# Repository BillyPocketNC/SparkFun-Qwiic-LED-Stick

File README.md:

SparkFun Qwiic LED Stick

This Design has been modified to make a 3x3 LED Matrix.
Sparkfun is the original source of the unmodified design.

========================================

[*Qwiic LED Stick (SPX-14783)*](https://www.sparkfun.com/products/14783)

The Qwiic LED Stick features ten addressable APA102 LEDs, making it easy to add full color LED control using I<sup>2</sup>C. Write to individual LEDs to display a count in binary, or write to the whole strip for cool lighting effects. We’ve written an Arduino library that takes care of the I<sup>2</sup>C and communication to the LEDs so all you have to do is decide what color each LED should be.

This board is one of our many [Qwiic](https://www.sparkfun.com/qwiic) compatible boards! Simply plug and go. No soldering, no figuring out which is SDA or SCL, and no voltage regulation or translation required!

SparkFun labored with love to create this code. Feel like supporting open source hardware? 
Buy a [board](https://www.sparkfun.com/products/14783) from SparkFun!

Repository Contents
-------------------

* **/Firmware** - Firmware
* **/Hardware** - Eagle design files (.brd, .sch)

Library
--------------
* **[Arduino Library](https://github.com/sparkfun/SparkFun_Qwiic_LED_Stick_Arduino_Library)** - Library for Qwiic LED Stick

License Information
-------------------

This product is _**open source**_! 

If you have any questions or concerns on licensing, please contact techsupport@sparkfun.com.

Please use, reuse, and modify these files as you see fit. Please maintain attribution to SparkFun Electronics and release any derivative under the same license.

Distributed as-is; no warranty is given.

- Your friends at SparkFun.

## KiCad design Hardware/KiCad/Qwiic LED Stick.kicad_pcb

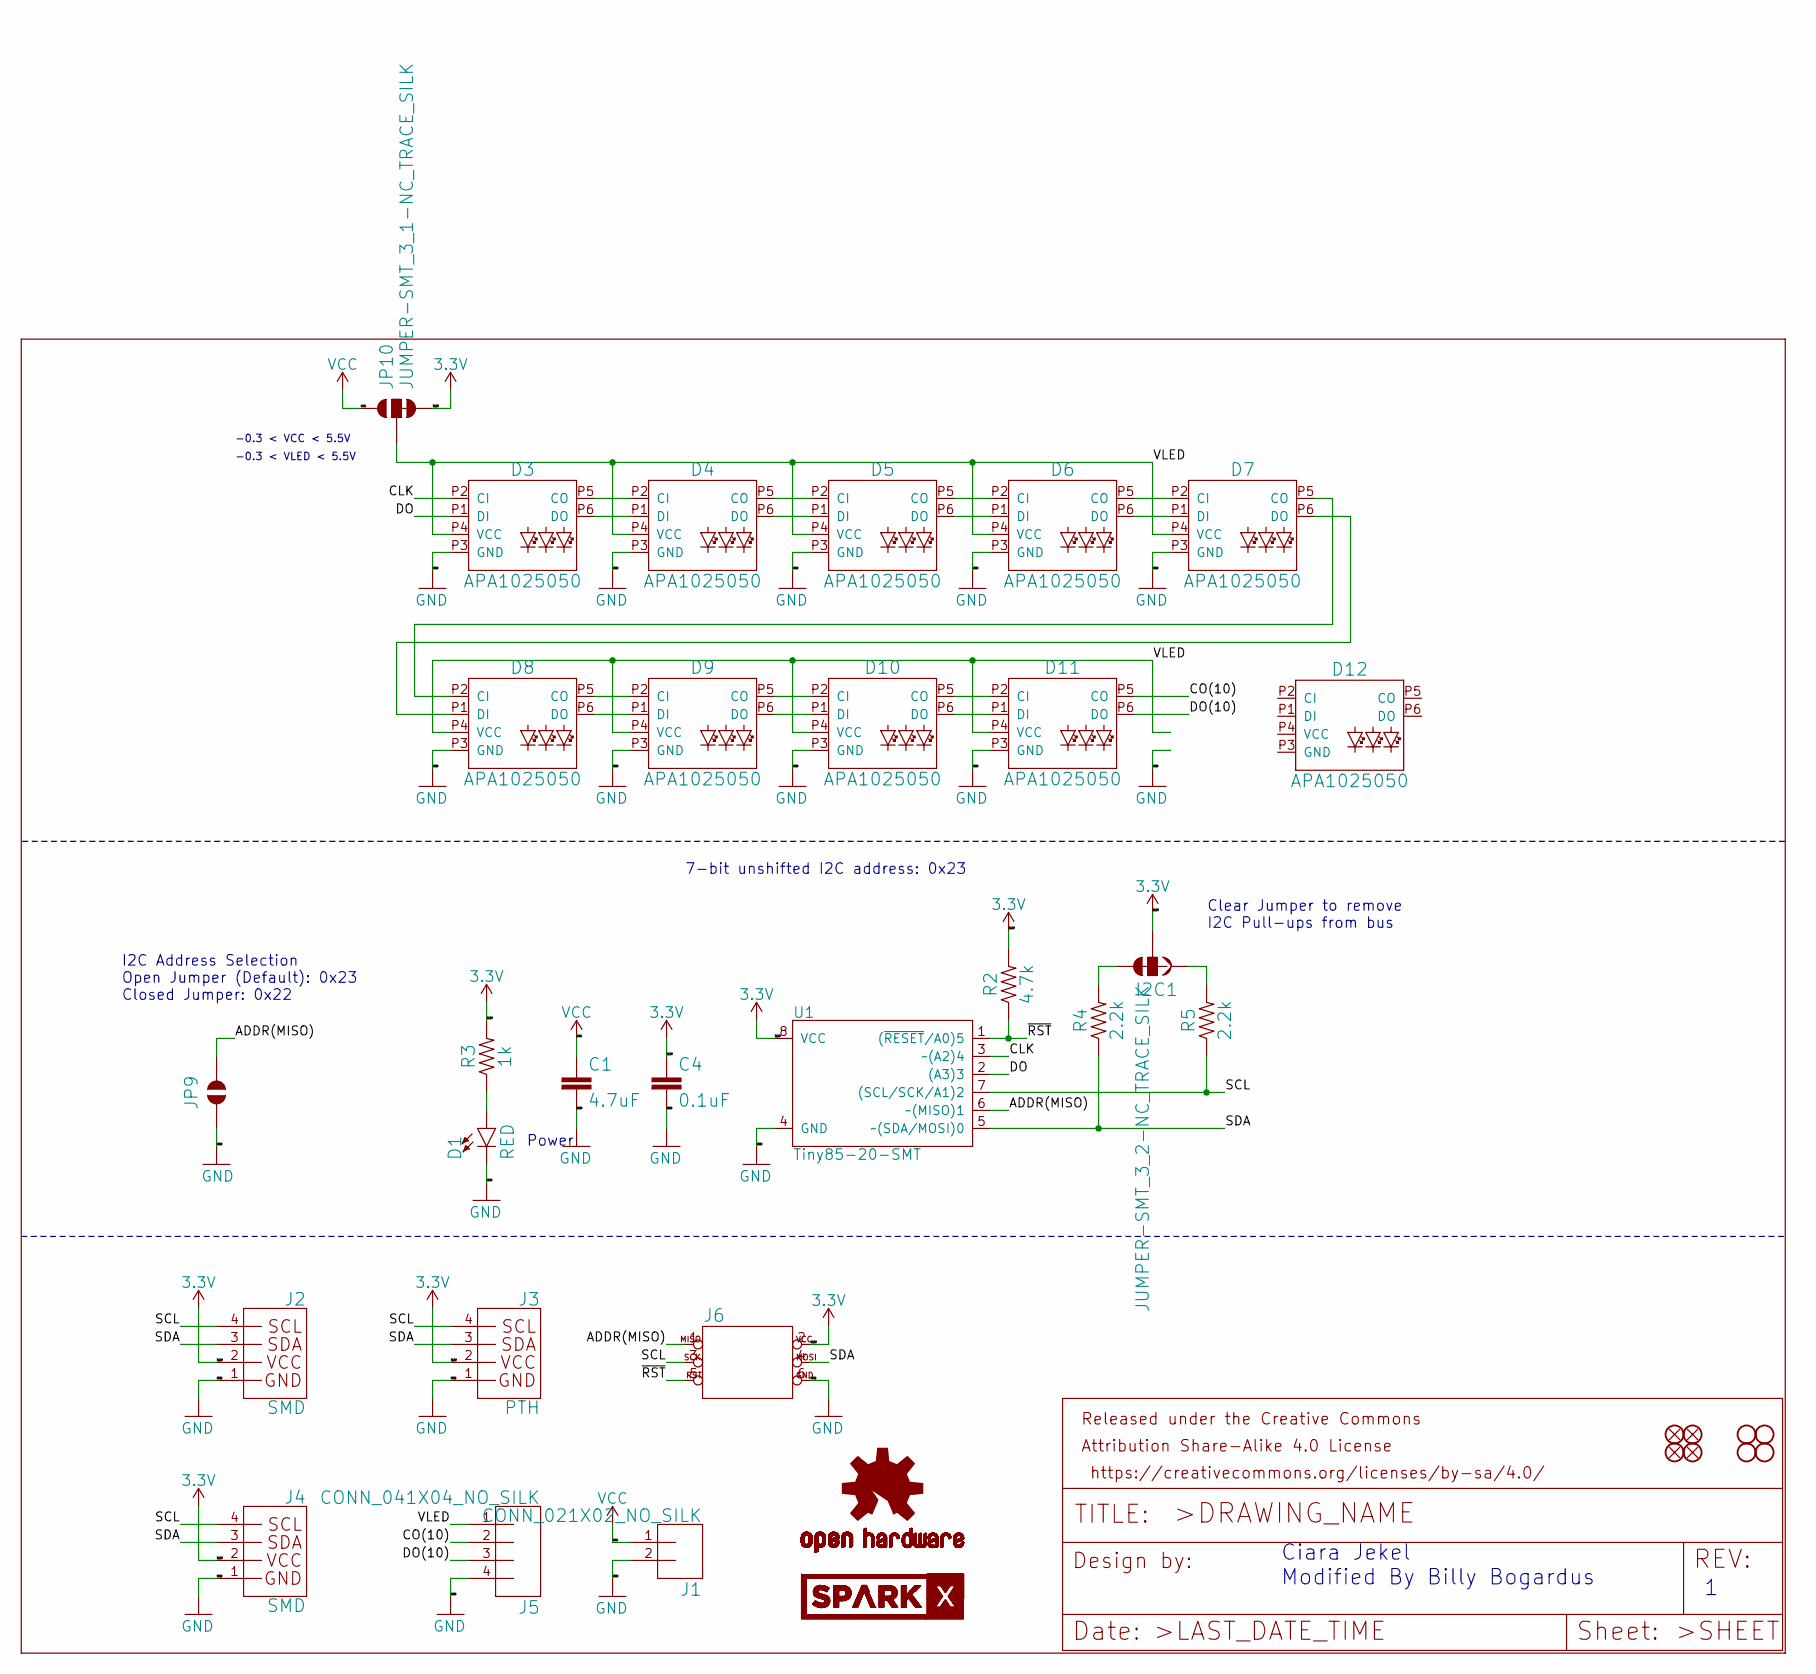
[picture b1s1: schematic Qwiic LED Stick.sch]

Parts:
C1: 4.7uF; 0603
C4: 0.1uF; 0603
D1: RED; LED-0603
D3, D4, D5, D6, D7, D8, D9, D10, D11, D12: APA1025050; APA102-5050
FRAME1: FRAME-LETTER; CREATIVE_COMMONS
I2C1: JUMPER-SMT_3_2-NC_TRACE_SILK; SMT-JUMPER_3_2-NC_TRACE_SILK
J1: CONN_021X02_NO_SILK; 1X02_NO_SILK
J2, J4: SMD; 1X04_1MM_RA
J3: PTH; 1X04_NO_SILK
J5: CONN_041X04_NO_SILK; 1X04_NO_SILK
J6: AVR_SPI_PROG_3X2TESTPOINTS; 2X3_TEST_POINTS
JP1, JP2, JP5, JP6: FIDUCIALUFIDUCIAL; MICRO-FIDUCIAL
JP3, JP4, JP7, JP8: STAND-OFF
JP9: JUMPER-SMT_2_NO_SILK; SMT-JUMPER_2_NO_SILK
JP10: JUMPER-SMT_3_1-NC_TRACE_SILK; SMT-JUMPER_3_1-NC_TRACE_SILK
LOGO1: OSHW-LOGOMINI; OSHW-LOGO-MINI
R2: 4.7k; 0603
R3: 1k; 0603
R4, R5: 2.2k; 0603
U1: Tiny85-20-SMT; SO08-EIAJ_MCU
U$1, U$2: SPARKX-LOGO4; SPARKX-MEDIUM

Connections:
3.3V: C4.1, I2C1.2, J2.2 (VCC), J3.2 (VCC), J4.2 (VCC), J6.2, JP10.3, R2.2, R3.2, U1.8 (VCC)
/ADDR(MISO): J6.1, JP9.2, U1.6 (~~(MISO)1)
/CLK: D3.P2 (CI), U1.3 (~~(A2)4)
/CO(10): D11.P5 (CO), J5.2
/DO: D3.P1 (DI), U1.2 ((A3)3)
/DO(10): D11.P6 (DO), J5.3
/SCL: J2.4 (SCL), J3.4 (SCL), J4.4 (SCL), J6.3, R5.1, U1.7 ((SCL/SCK/A1)2)
/SDA: J2.3 (SDA), J3.3 (SDA), J4.3 (SDA), J6.4, R4.1, U1.5 (~~(SDA/MOSI)0)
/VLED: D3.P4 (VCC), D4.P4 (VCC), D5.P4 (VCC), D6.P4 (VCC), D7.P4 (VCC), D8.P4 (VCC), D9.P4 (VCC), D10.P4 (VCC), D11.P4 (VCC), J5.1, JP10.2
/~RST: J6.5, R2.1, U1.1 ((~RESET~/A0)5)
GND: C1.2, C4.2, D1.C, D3.P3 (GND), D4.P3 (GND), D5.P3 (GND), D6.P3 (GND), D7.P3 (GND), D8.P3 (GND), D9.P3 (GND), D10.P3 (GND), D11.P3 (GND), J1.2, J2.1 (GND), J3.1 (GND), J4.1 (GND), J5.4, J6.6, JP9.1, U1.4 (GND)
unnamed: D1.A, R3.1
unnamed: D3.P5 (CO), D4.P2 (CI)
unnamed: D3.P6 (DO), D4.P1 (DI)
unnamed: D4.P5 (CO), D5.P2 (CI)
unnamed: D4.P6 (DO), D5.P1 (DI)
unnamed: D5.P5 (CO), D6.P2 (CI)
unnamed: D5.P6 (DO), D6.P1 (DI)
unnamed: D6.P5 (CO), D7.P2 (CI)
unnamed: D6.P6 (DO), D7.P1 (DI)
unnamed: D7.P5 (CO), D8.P2 (CI)
unnamed: D7.P6 (DO), D8.P1 (DI)
unnamed: D8.P5 (CO), D9.P2 (CI)
unnamed: D8.P6 (DO), D9.P1 (DI)
unnamed: D9.P6 (DO), D10.P1 (DI)
unnamed: D9.P5 (CO), D10.P2 (CI)
unnamed: D10.P5 (CO), D11.P2 (CI)
unnamed: D10.P6 (DO), D11.P1 (DI)
unnamed: I2C1.1, R5.2
unnamed: I2C1.3, R4.2
VCC: C1.1, J1.1, JP10.1

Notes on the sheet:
Clear Jumper to remove I2C Pull-ups from bus
Power
Ciara Jekel Modified By Billy Bogardus
7-bit unshifted I2C address: 0x23
I2C Address Selection Open Jumper (Default): 0x23 Closed Jumper: 0x22
-0.3 < VCC < 5.5V
-0.3 < VLED < 5.5V

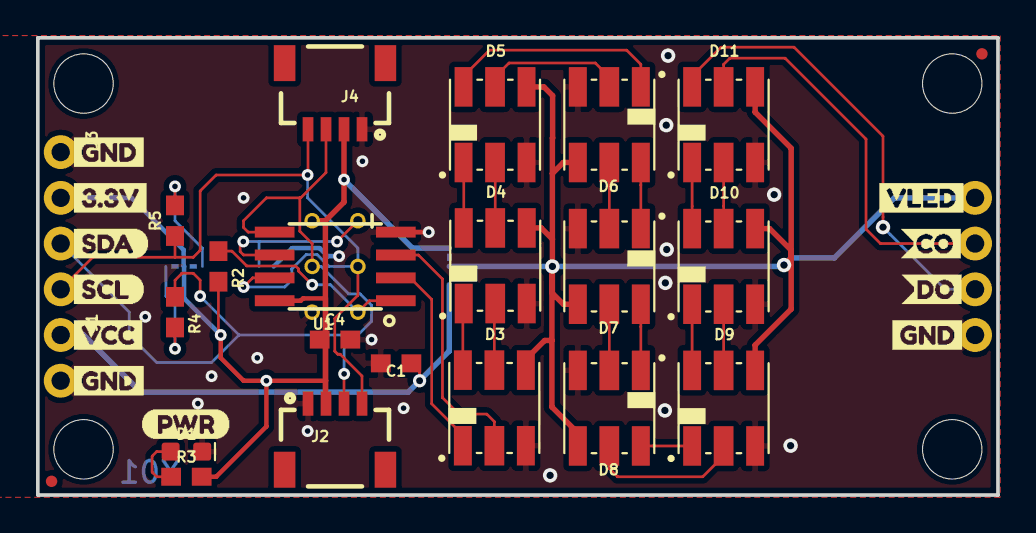
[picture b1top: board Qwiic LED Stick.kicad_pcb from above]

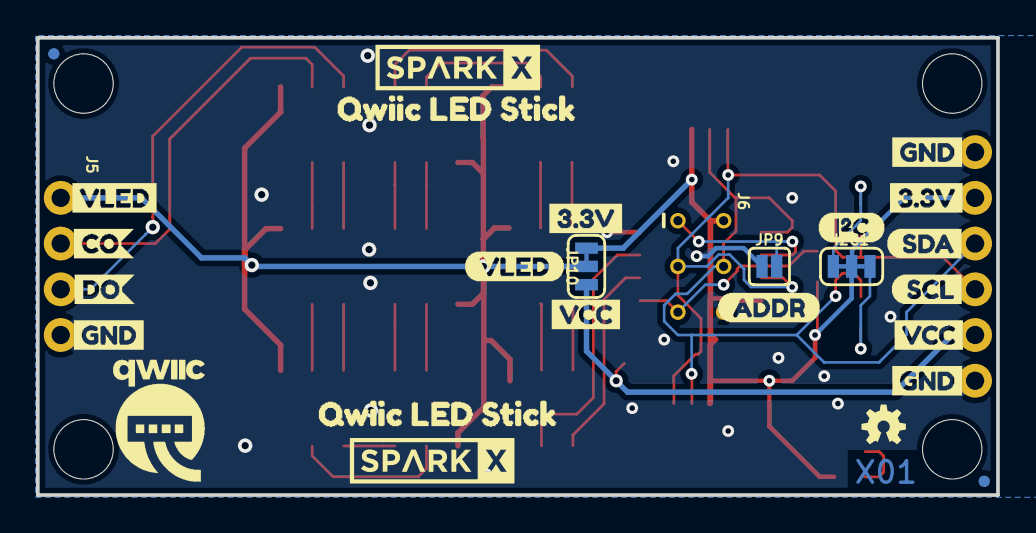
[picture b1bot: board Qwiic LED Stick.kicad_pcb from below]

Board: 2 copper layers, 53.3 x 25.4 mm, 67 parts (28 on the bottom side), 31 nets.

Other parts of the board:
U$3, U$8, U$12, U$22: GND1
U$4, U$21: 3#3V2
U$5, U$9: VLED4
U$6: DO8
U$7: CO5
U$10: (PWR)
U$11: (I_SUPER2_C)
U$13, U$32: QWIIC_LED_STICK1
U$15: DO12
U$16: CO9
U$17: SDA0
U$18: SCL1
U$19, U$20, U$31: VCC1
U$23, U$24: GND0
U$25: VLED3
U$26: SCL9
U$27: SDA8
U$28: ADDR2
U$29: QWIIC-LOGO-MEDIUM
U$30: 3#3V3

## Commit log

2019-12-05 moved Eagel files to sub folder
2019-12-05 Converted to KiCad
2019-12-05 applied Our design rules only moved two traces
2019-12-05 atempted creating BOM - need to order parts manually
2019-12-05 created a smaller Board
2019-12-05 Removed 2 inner layers
2019-12-05 moved a fram and a few dividing lines in the schematic
2020-01-02 added a few Vias to the Ground Plane to reduce ground loops
2020-01-15 Updated Footprint for APA102-505 Cleaned up fab layer for readability

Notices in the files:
parts and their libraries:
https://creativecommons.org/licenses/by-sa/4.0
Released under the Creative Commons Attribution Share-Alike 4.0 License
